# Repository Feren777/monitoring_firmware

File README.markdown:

About Monitoring
================
This project aims to bring internet connectivity to rainwater treatment products. Monitoring is the automated process by which measurements and condition analysis of a rainwater harvesting system is transmitted over remote networks. Telemetry is important in rainwater management, not only for quality and gauging of water but mainly for reliability, health and usage of local equipment in difficult or inaccessible areas.

Based on Ethersex
=================
Ethersex, originally developed to provide an alternative firmware for the [etherrape hardware](http://www.lochraster.org/etherrape),
evolved into a full-featured still light-weight firmware for the Atmel megaAVR processors.  
For more information and a comprehensive documentation  consult [http://www.ethersex.de](http://www.ethersex.de)!

How to configure the firmware
=============================
Make sure that you meet the requirements.  
Copy/rename one of the predefined configuration files aqualoop.config or rainmaster.config to .config
Use `make menuconfig` to configure and `make` to compile the firmware.
The final hex file is named `ethersex.hex`.

[See the Quick Start Guide in the wiki for more information](http://ethersex.de/index.php/Quick_Start_Guide)

How to add a new hardware pinning
=================================
Currently only AQUALOOP and RAINMASTER units are ported.
Use the script at `scripts/add-hardware` to add a new pinning.

Used 3rd party software 
=======================
This program contains software by other authors:

* [the uIP tcp/ip stack](http://www.sics.se/~adam/uip) in the directory `/protocols/uip/`, written by Adam Dunkels
* [usb-software stack from obdev](http://www.obdev.at/products/vusb/index.html) in `/protocols/usb/usbdrv/`
* [sd card reader](http://www.roland-riegel.de/sd-reader/index.html) in `/hardware/storage/sd_reader`

License
=======
All code is licensed under GPLv3, unless otherwise noted. See COPYING in the main
directory, but in doubt check the file header. Usually every file contains a
header, stating all contributing authors and the specific license used.

Various make targets
====================

* `make show-config` -- Shows the activated modules

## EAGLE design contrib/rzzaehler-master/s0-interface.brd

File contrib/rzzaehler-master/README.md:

rzzaehler
=========

Energy counter for the Serverroom of shackspace, implemented using ethersex, ehterrape and some wiring :)

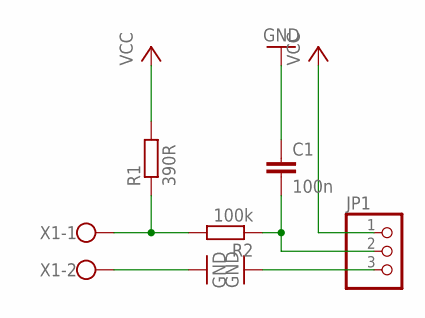
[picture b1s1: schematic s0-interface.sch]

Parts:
C1: 100n; C0603
JP1: PINHD-1X3; 1X03
R1: 390R; R0603
R2: 100k; R0603
X1: W237-102

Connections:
GND: C1.1, JP1.3, X1.2
unnamed: R1.1, R2.2, X1.1
unnamed: C1.2, JP1.2, R2.1
VCC: JP1.1, R1.2

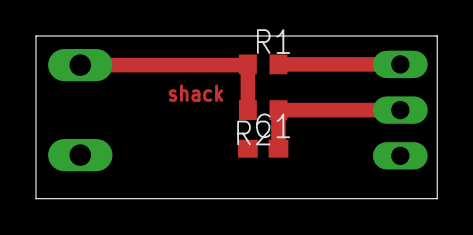
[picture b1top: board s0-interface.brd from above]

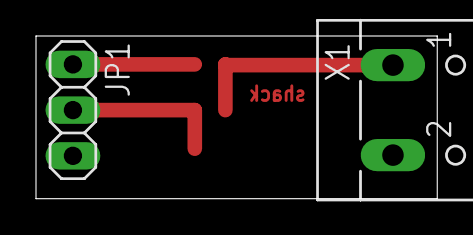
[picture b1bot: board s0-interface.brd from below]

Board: 2 copper layers, 22.3 x 9.0 mm, 5 parts (2 on the bottom side), 4 nets.

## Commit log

2016-06-14 Renamed config files
2016-09-08 Demoanlage Kelmis
